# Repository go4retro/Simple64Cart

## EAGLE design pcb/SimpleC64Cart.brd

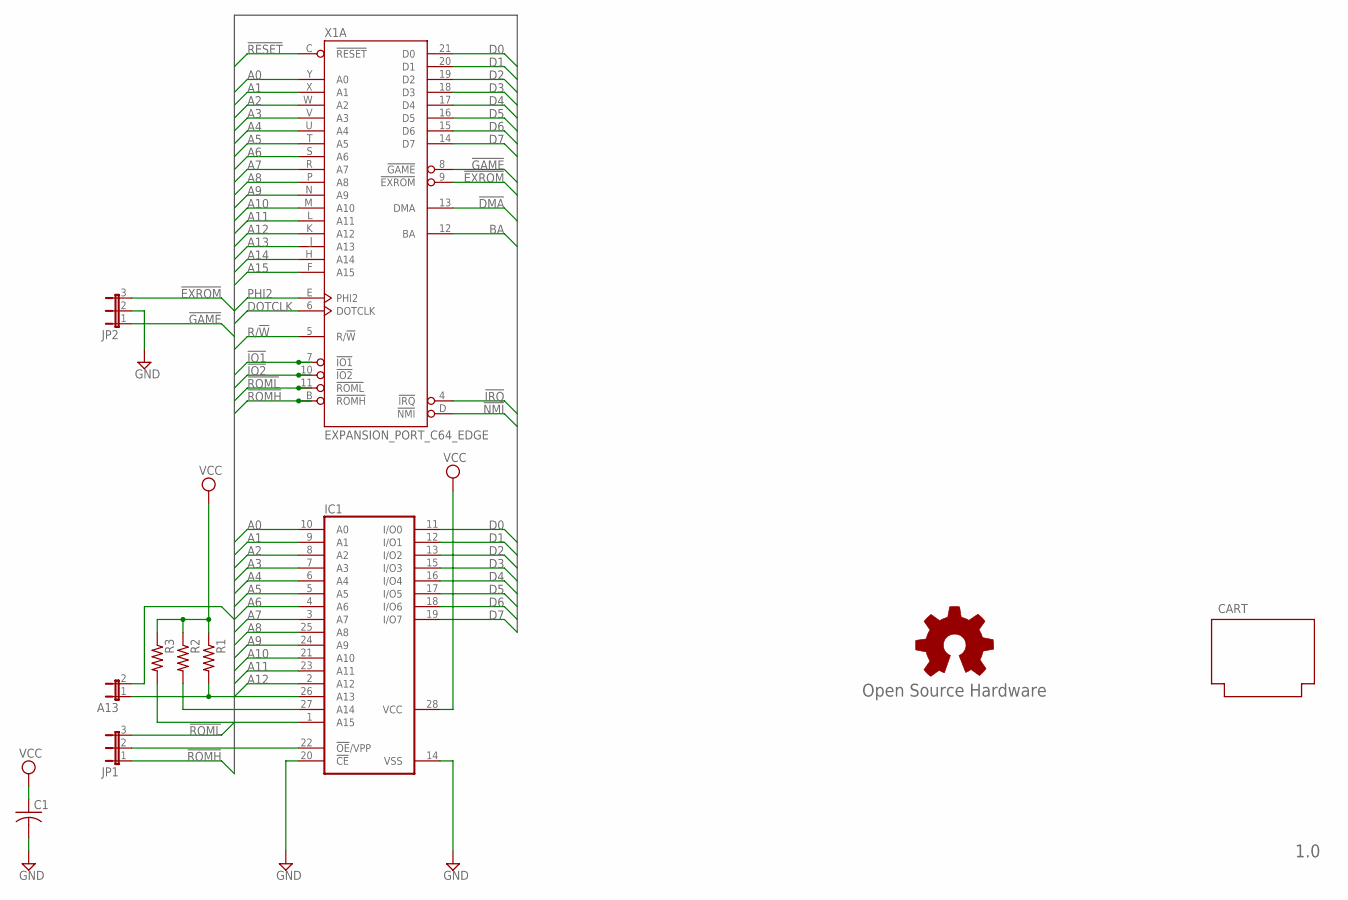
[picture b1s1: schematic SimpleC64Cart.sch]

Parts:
A13: JP1E; JP1
C1: C-US025-025X050; C025-025X050
CART: CARTRIDGE_C64
GOLD_ORB_SM1: Open Source Hardware; OSHW_8MM
IC1: 27512G; DIL28-6
JP1, JP2: JP2E; JP2
R1, R2, R3: R-US_0204/7; 0204/7
X1: EXPANSION_PORT_C64_EDGE; MA100-22-2

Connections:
!DMA: X1.13 (DMA)
!EXROM: JP2.3, X1.9 (!EXROM)
!GAME: JP2.1, X1.8 (!GAME)
!IO1: X1.7 (!IO1)
!IO2: X1.10 (!IO2)
!IRQ: X1.4 (!IRQ)
!NMI: X1.D (!NMI)
!RESET: X1.C (!RESET)
!ROMH: JP1.1, X1.B (!ROMH)
!ROML: JP1.3, X1.11 (!ROML)
A0: IC1.10 (A0), X1.Y (A0)
A1: IC1.9 (A1), X1.X (A1)
A2: IC1.8 (A2), X1.W (A2)
A3: IC1.7 (A3), X1.V (A3)
A4: IC1.6 (A4), X1.U (A4)
A5: IC1.5 (A5), X1.T (A5)
A6: IC1.4 (A6), X1.S (A6)
A7: IC1.3 (A7), X1.R (A7)
A8: IC1.25 (A8), X1.P (A8)
A9: IC1.24 (A9), X1.N (A9)
A10: IC1.21 (A10), X1.M (A10)
A11: IC1.23 (A11), X1.L (A11)
A12: IC1.2 (A12), X1.K (A12)
A13: A13.2, X1.J (A13)
A14: X1.H (A14)
A15: X1.F (A15)
ADDR13: A13.1, IC1.26 (A13), R1.2
ADDR14: IC1.27 (A14), R2.2
ADDR15: IC1.1 (A15), R3.2
BA: X1.12 (BA)
D0: IC1.11 (I/O0), X1.21 (D0)
D1: IC1.12 (I/O1), X1.20 (D1)
D2: IC1.13 (I/O2), X1.19 (D2)
D3: IC1.15 (I/O3), X1.18 (D3)
D4: IC1.16 (I/O4), X1.17 (D4)
D5: IC1.17 (I/O5), X1.16 (D5)
D6: IC1.18 (I/O6), X1.15 (D6)
D7: IC1.19 (I/O7), X1.14 (D7)
DOTCLK: X1.6 (DOTCLK)
GND: C1.2, IC1.14 (VSS), IC1.20 (!CE), JP2.2, X1.1 (GND), X1.22 (GND), X1.A (GND), X1.Z (GND)
unnamed: IC1.22 (!OE!/VPP), JP1.2
PHI2: X1.E (PHI2)
R/!W: X1.5 (R/!W)
VCC: C1.1, IC1.28 (VCC), R1.1, R2.1, R3.1, X1.2 (VCC), X1.3 (VCC)

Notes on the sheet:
1.0

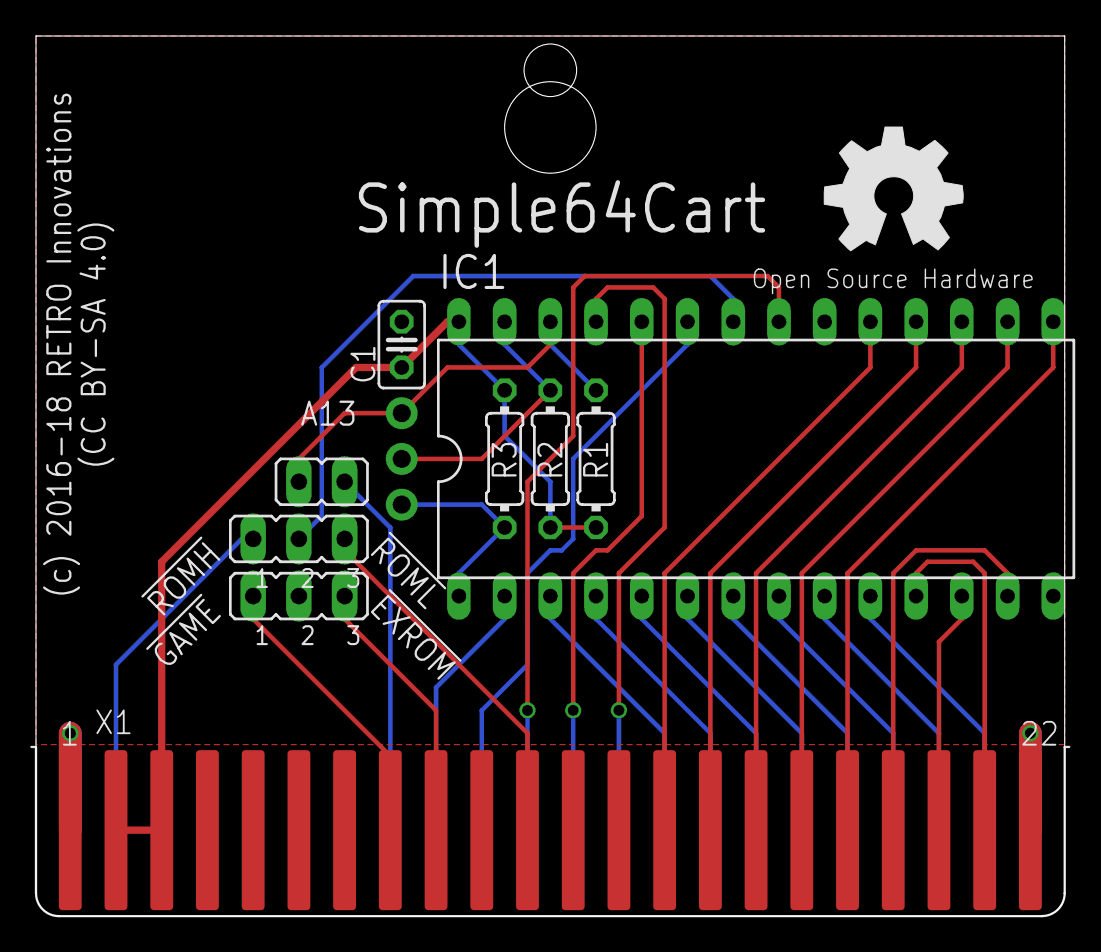
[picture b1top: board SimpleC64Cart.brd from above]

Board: 2 copper layers, 57.1 x 48.9 mm, 11 parts (0 on the bottom side), 32 nets.

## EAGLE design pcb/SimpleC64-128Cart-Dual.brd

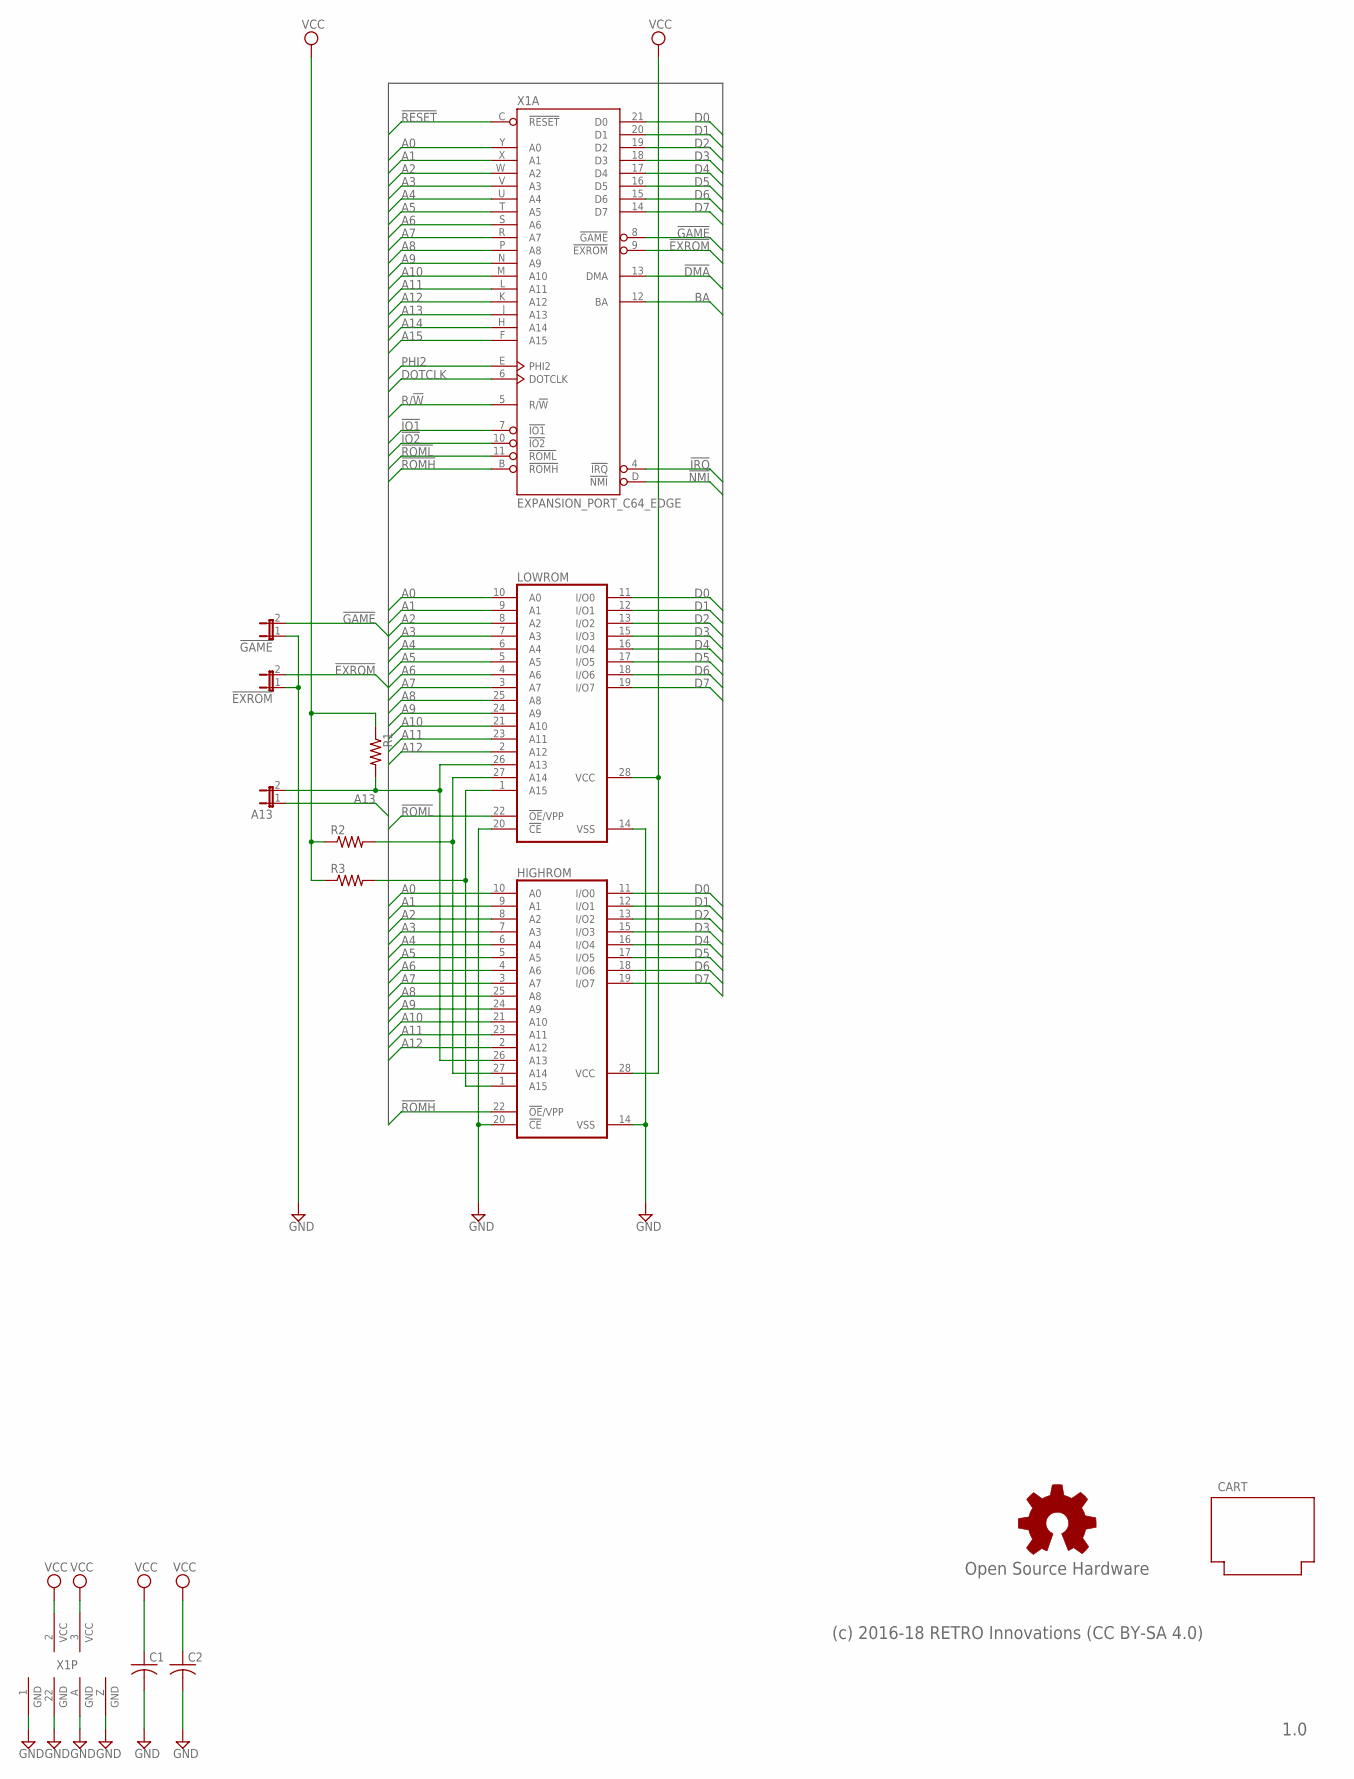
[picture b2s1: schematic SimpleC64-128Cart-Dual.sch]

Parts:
!EXROM: JP1E; JP1
!GAME: JP1E; JP1
A13: JP1E; JP1
C1, C2: C-US025-025X050; C025-025X050
CART: CARTRIDGE_C64
GOLD_ORB_SM1: Open Source Hardware; OSHW_8MM
HIGHROM: 27512G; DIL28-6
LOWROM: 27512G; DIL28-6
R1, R2, R3: R-US_0204/7; 0204/7
X1: EXPANSION_PORT_C64_EDGE; MA100-22-2

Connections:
!DMA: X1.13 (DMA)
!EXROM: !EXROM.2, X1.9 (!EXROM)
!GAME: !GAME.2, X1.8 (!GAME)
!IO1: X1.7 (!IO1)
!IO2: X1.10 (!IO2)
!IRQ: X1.4 (!IRQ)
!NMI: X1.D (!NMI)
!RESET: X1.C (!RESET)
!ROMH: HIGHROM.22 (!OE!/VPP), X1.B (!ROMH)
!ROML: LOWROM.22 (!OE!/VPP), X1.11 (!ROML)
A0: HIGHROM.10 (A0), LOWROM.10 (A0), X1.Y (A0)
A1: HIGHROM.9 (A1), LOWROM.9 (A1), X1.X (A1)
A2: HIGHROM.8 (A2), LOWROM.8 (A2), X1.W (A2)
A3: HIGHROM.7 (A3), LOWROM.7 (A3), X1.V (A3)
A4: HIGHROM.6 (A4), LOWROM.6 (A4), X1.U (A4)
A5: HIGHROM.5 (A5), LOWROM.5 (A5), X1.T (A5)
A6: HIGHROM.4 (A6), LOWROM.4 (A6), X1.S (A6)
A7: HIGHROM.3 (A7), LOWROM.3 (A7), X1.R (A7)
A8: HIGHROM.25 (A8), LOWROM.25 (A8), X1.P (A8)
A9: HIGHROM.24 (A9), LOWROM.24 (A9), X1.N (A9)
A10: HIGHROM.21 (A10), LOWROM.21 (A10), X1.M (A10)
A11: HIGHROM.23 (A11), LOWROM.23 (A11), X1.L (A11)
A12: HIGHROM.2 (A12), LOWROM.2 (A12), X1.K (A12)
A13: A13.1, X1.J (A13)
A14: X1.H (A14)
A15: X1.F (A15)
ADDR13: A13.2, HIGHROM.26 (A13), LOWROM.26 (A13), R1.2
ADDR14: HIGHROM.27 (A14), LOWROM.27 (A14), R2.2
ADDR15: HIGHROM.1 (A15), LOWROM.1 (A15), R3.2
BA: X1.12 (BA)
D0: HIGHROM.11 (I/O0), LOWROM.11 (I/O0), X1.21 (D0)
D1: HIGHROM.12 (I/O1), LOWROM.12 (I/O1), X1.20 (D1)
D2: HIGHROM.13 (I/O2), LOWROM.13 (I/O2), X1.19 (D2)
D3: HIGHROM.15 (I/O3), LOWROM.15 (I/O3), X1.18 (D3)
D4: HIGHROM.16 (I/O4), LOWROM.16 (I/O4), X1.17 (D4)
D5: HIGHROM.17 (I/O5), LOWROM.17 (I/O5), X1.16 (D5)
D6: HIGHROM.18 (I/O6), LOWROM.18 (I/O6), X1.15 (D6)
D7: HIGHROM.19 (I/O7), LOWROM.19 (I/O7), X1.14 (D7)
DOTCLK: X1.6 (DOTCLK)
GND: !EXROM.1, !GAME.1, C1.2, C2.2, HIGHROM.14 (VSS), HIGHROM.20 (!CE), LOWROM.14 (VSS), LOWROM.20 (!CE), X1.1 (GND), X1.22 (GND), X1.A (GND), X1.Z (GND)
PHI2: X1.E (PHI2)
R/!W: X1.5 (R/!W)
VCC: C1.1, C2.1, HIGHROM.28 (VCC), LOWROM.28 (VCC), R1.1, R2.1, R3.1, X1.2 (VCC), X1.3 (VCC)

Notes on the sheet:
1.0
(c) 2016-18 RETRO Innovations (CC BY-SA 4.0)

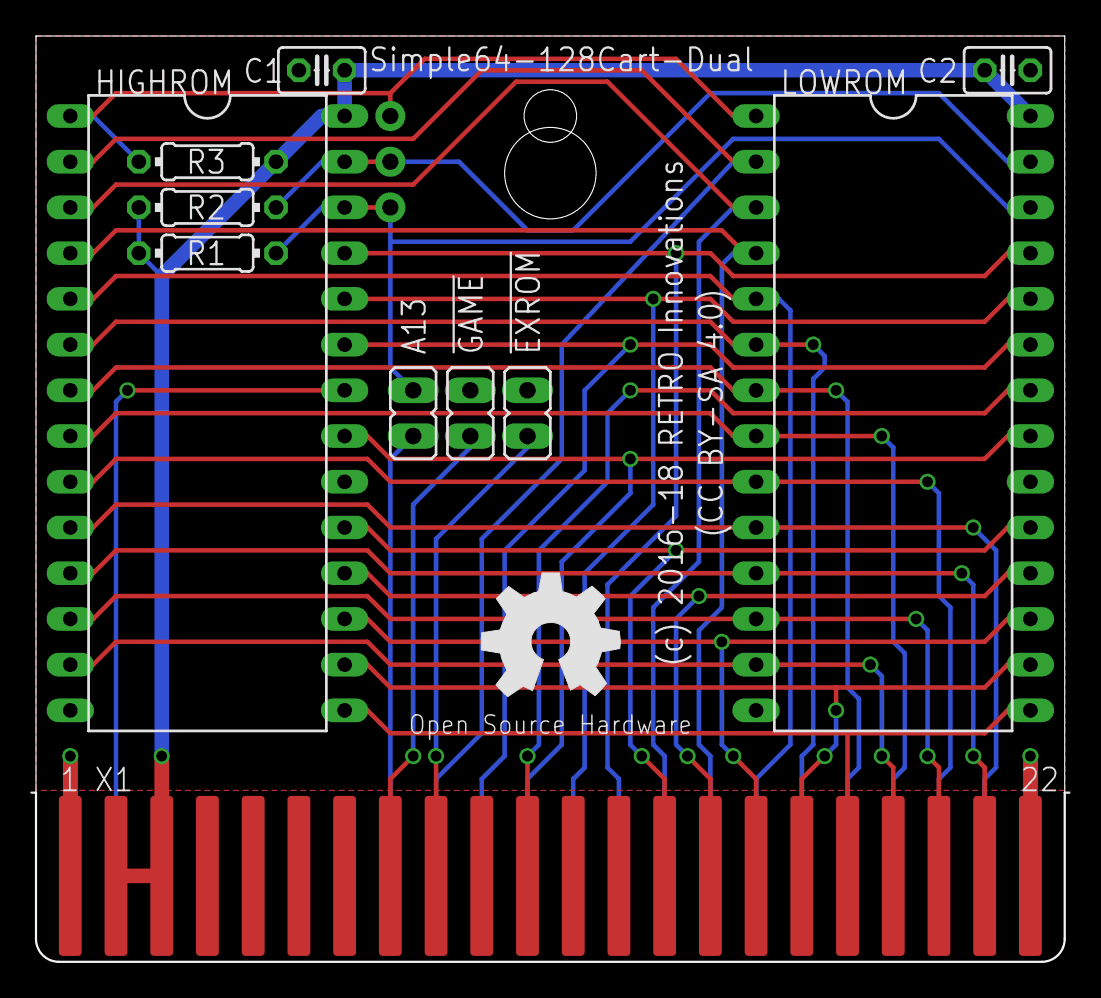
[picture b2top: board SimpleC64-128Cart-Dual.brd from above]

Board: 2 copper layers, 57.1 x 51.4 mm, 13 parts (0 on the bottom side), 31 nets.
